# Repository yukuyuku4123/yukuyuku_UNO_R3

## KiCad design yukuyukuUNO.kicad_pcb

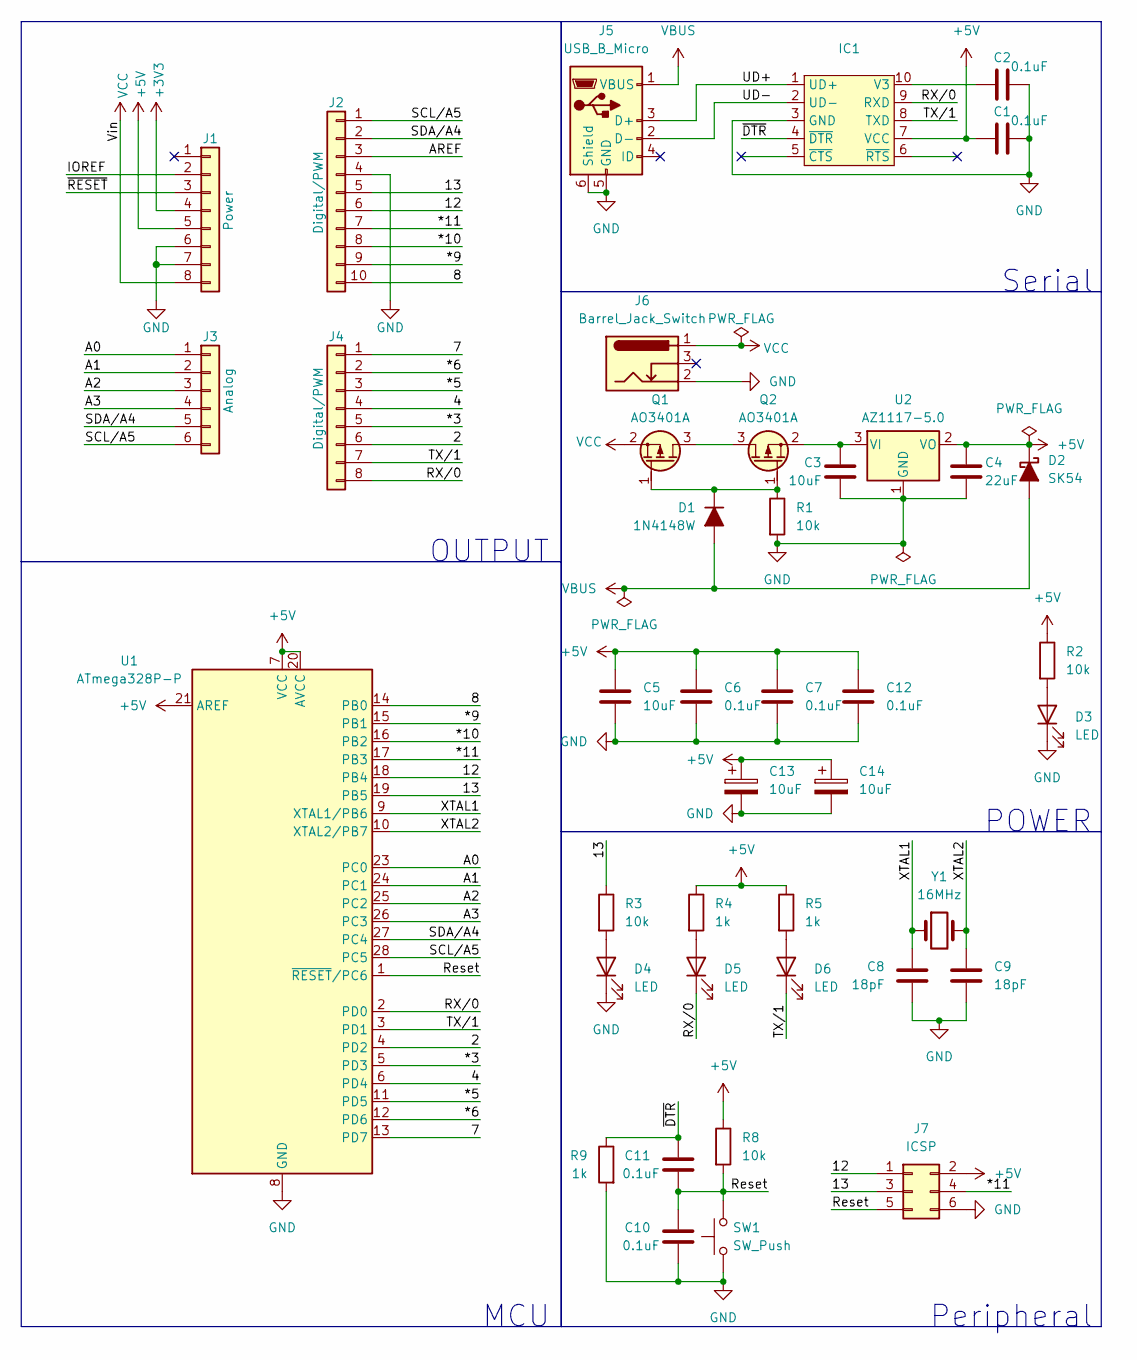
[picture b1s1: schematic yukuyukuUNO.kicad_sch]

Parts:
C1, C2, C6, C7, C10, C11, C12: 0.1uF; C_0603_1608Metric
C3, C5: 10uF; C_0603_1608Metric
C4: 22uF; C_0603_1608Metric
C8, C9: 18pF; C_0402_1005Metric
C13, C14: 10uF; C_Elec_5x5.4
D1: 1N4148W; D_SOD-123
D2: SK54; D_SMB
D3, D4, D5, D6: LED; LED_0603_1608Metric
IC1: SSOP-10_3.9x4.9mm_P1.00mm
J1: Power; PinSocket_1x08_P2.54mm_Vertical
J2: Digital/PWM; PinSocket_1x10_P2.54mm_Vertical
J3: Analog; PinSocket_1x06_P2.54mm_Vertical
J4: Digital/PWM; PinSocket_1x08_P2.54mm_Vertical
J5: USB_B_Micro; USB_Micro-B_Molex_47346-0001
J6: Barrel_Jack_Switch; BarrelJack_Horizontal
J7: ICSP; PinHeader_2x03_P2.54mm_Vertical
Q1, Q2: AO3401A; TSOT-23
R1, R2, R3, R8: 10k; R_0603_1608Metric
R4, R5, R9: 1k; R_0603_1608Metric
SW1: SW_Push; SW_PUSH_6mm
U1: ATmega328P-P; DIP-28_W7.62mm
U2: AZ1117-5.0; TO-252-2
Y1: 16MHz; Crystal_HC49-4H_Vertical

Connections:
+3V3: J1.4
+5V: C1.1, C4.1, C5.1, C6.1, C7.1, C12.1, C13.1, C14.1, D2.1 (K), IC1.7 (VCC), J1.5, J7.2, R2.1, R4.1, R5.1, R8.1, U1.7 (VCC), U1.20 (AVCC), U1.21 (AREF), U2.2 (VO)
/2: J4.6, U1.4 (PD2)
/4: J4.4, U1.6 (PD4)
/7: J4.1, U1.13 (PD7)
/8: J2.10, U1.14 (PB0)
/12: J2.6, J7.1, U1.18 (PB4)
/13: J2.5, J7.3, R3.1, U1.19 (PB5)
/*3: J4.5, U1.5 (PD3)
/*5: J4.3, U1.11 (PD5)
/*6: J4.2, U1.12 (PD6)
/*9: J2.9, U1.15 (PB1)
/*10: J2.8, U1.16 (PB2)
/*11: J2.7, J7.4, U1.17 (PB3)
/A0: J3.1, U1.23 (PC0)
/A1: J3.2, U1.24 (PC1)
/A2: J3.3, U1.25 (PC2)
/A3: J3.4, U1.26 (PC3)
/AREF: J2.3
/IOREF: J1.2
/RX/0: D5.1 (K), IC1.9 (RXD), J4.8, U1.2 (PD0)
/Reset: C10.1, C11.2, J7.5, R8.2, SW1.2, U1.1 (~RESET/PC6)
/SCL/A5: J2.1, J3.6, U1.28 (PC5)
/SDA/A4: J2.2, J3.5, U1.27 (PC4)
/TX/1: D6.1 (K), IC1.8 (TXD), J4.7, U1.3 (PD1)
/UD+: IC1.1 (UD+), J5.3 (D+)
/UD-: IC1.2 (UD-), J5.2 (D-)
/XTAL1: C8.1, U1.9 (XTAL1/PB6), Y1.1
/XTAL2: C9.1, U1.10 (XTAL2/PB7), Y1.2
/~DTR: C11.1, IC1.4 (~DTR), R9.1
/~RESET: J1.3
GND: C1.2, C2.2, C3.2, C4.2, C5.2, C6.2, C7.2, C8.2, C9.2, C10.2, C12.2, C13.2, C14.2, D3.1 (K), D4.1 (K), IC1.3 (GND), J1.6, J1.7, J2.4, J5.5 (GND), J5.6 (Shield), J6.2, J7.6, R1.2, R9.2, SW1.1, U1.8 (GND), U1.22 (GND), U2.1 (GND)
unnamed: D1.1 (K), Q1.1 (G), Q2.1 (G), R1.1
unnamed: D3.2 (A), R2.2
unnamed: D4.2 (A), R3.2
unnamed: D5.2 (A), R4.2
unnamed: D6.2 (A), R5.2
unnamed: C2.1, IC1.10 (V3)
unnamed: Q1.3 (D), Q2.3 (D)
unnamed: C3.1, Q2.2 (S), U2.3 (VI)
VBUS: D1.2 (A), D2.2 (A), J5.1 (VBUS)
VCC: J1.8, J6.1, Q1.2 (S)

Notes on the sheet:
OUTPUT
Serial
POWER
Peripheral
MCU

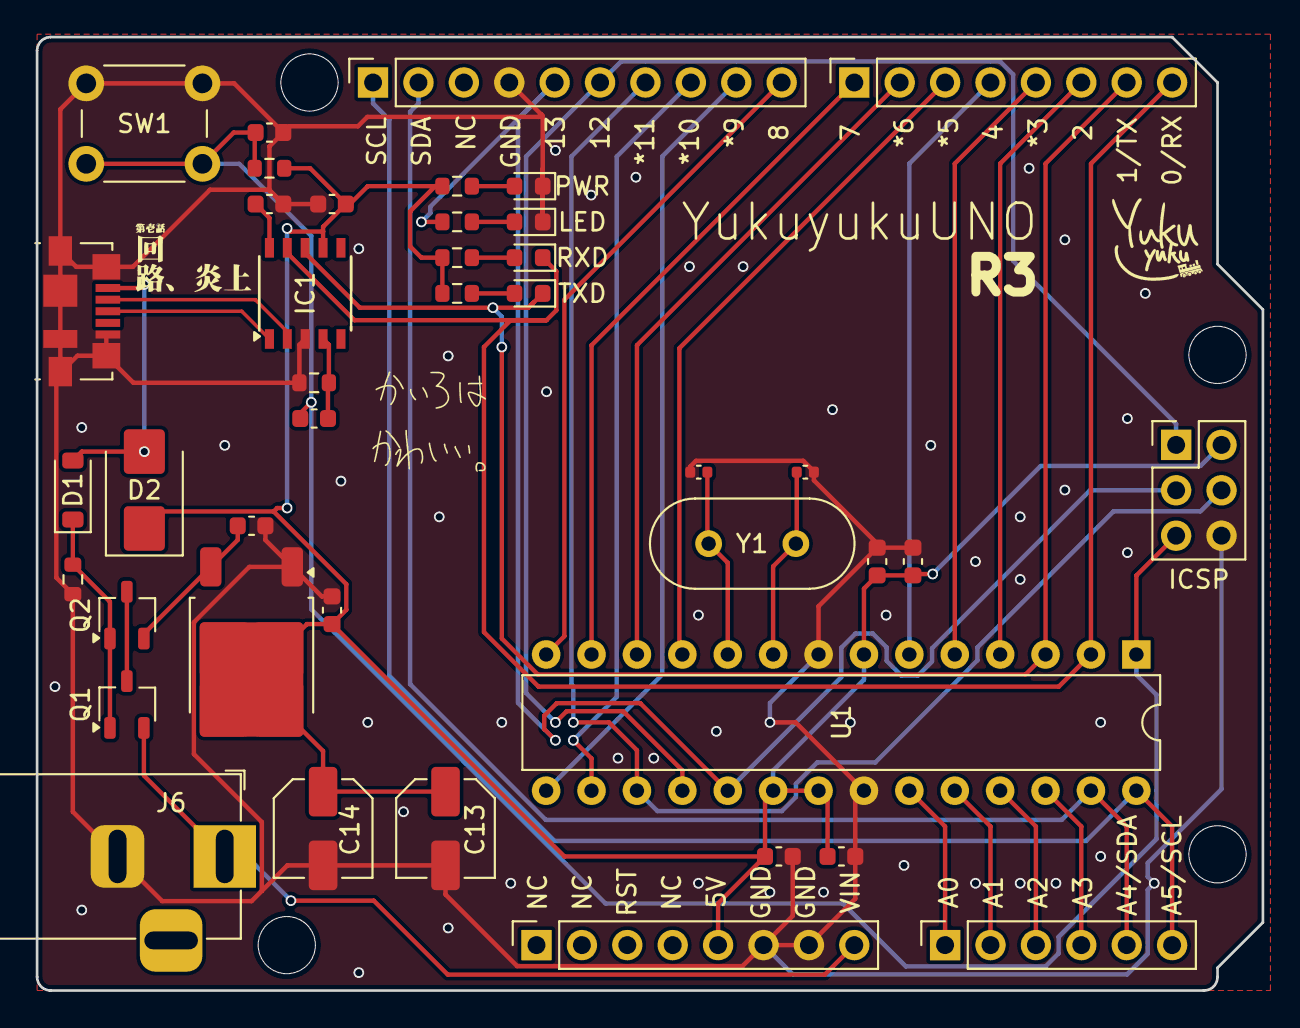
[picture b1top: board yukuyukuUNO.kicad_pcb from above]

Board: 2 copper layers, 68.6 x 53.3 mm, 45 parts (0 on the bottom side), 38 nets.

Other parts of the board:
MH1, MH2, MH3, MH4: MountingHole_3.2mm

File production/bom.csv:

Designator,Footprint,Quantity,Value,LCSC Part #
"C1, C10, C11, C12, C2, C6, C7",0603,7,0.1uF,
"C13, C14",C_Elec_5x5.4,2,10uF,
"C3, C5",0603,2,10uF,
C4,0603,1,22uF,
"C8, C9",0402,2,18pF,
D1,D_SOD-123,1,1N4148W,
D2,D_SMB,1,SK54,
"D3, D4, D5, D6",0603,4,LED,
IC1,SSOP-10_3.9x4.9mm_P1.00mm,1,~,
J1,PinSocket_1x08_P2.54mm_Vertical,1,Power,
J2,PinSocket_1x10_P2.54mm_Vertical,1,Digital/PWM,
J3,PinSocket_1x06_P2.54mm_Vertical,1,Analog,
J4,PinSocket_1x08_P2.54mm_Vertical,1,Digital/PWM,
J5,USB_Micro-B_Molex_47346-0001,1,USB_B_Micro,
J6,BarrelJack_Horizontal,1,Barrel_Jack_Switch,
J7,PinHeader_2x03_P2.54mm_Vertical,1,ICSP,
"Q1, Q2",TSOT-23,2,AO3401A,
"R1, R2, R3, R8",0603,4,10k,
"R4, R5, R9",0603,3,1k,
SW1,SW_PUSH_6mm,1,SW_Push,
U1,DIP-28_W7.62mm,1,ATmega328P-P,
U2,TO-252-2,1,AZ1117-5.0,
Y1,Crystal_HC49-4H_Vertical,1,16MHz,

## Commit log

2024-07-30 Ver-1.0
2024-07-30 Create LICENSE
